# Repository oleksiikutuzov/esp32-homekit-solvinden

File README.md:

# esp32-homekit-led-strip
Native Apple HomeKit via an ESP32 for the IKEA SOLVINDEN lamp

Software is based on the [HomeSpan](https://github.com/HomeSpan/HomeSpan) library. Supports RGB or RGBW Neopixel LEDs.

_As usual, don't expect any warranties. I am just a hobbyist, not a professional. It works for me, but you take your own risk using it. I am not liable for any damage to your devices._

## Hardware

Custom PCB is designed for the project as well as a replacement base for the lamp. The base has holes for M3 threaded inserts.

From the original lamp, you only need the top part, which is good for diffusion. Be careful not to scratch it, as it sits pretty tight because the device is sealed.

## HomeKit functions

The device has two modes, which can be switched via the Eve app:
* Manual Control (manually set one single color)
* Rainbow (the device is changing colors)

*As they are custom characteristics, they are not visible in the Home app*

Characteristics values are saved to NVS, so they will be restored if the device loses power. 

## Software

Here you can see, which pins are used and pre-defined in the firmware:
```c++
 *                ESP-WROOM-32 Utilized pins
 *              ╔═════════════════════════════╗
 *              ║┌─┬─┐  ┌──┐  ┌─┐             ║
 *              ║│ | └──┘  └──┘ |             ║
 *              ║│ |            |             ║
 *              ╠═════════════════════════════╣
 *          +++ ║GND                       GND║ +++
 *          +++ ║3.3V                     IO23║ USED_FOR_NOTHING
 *              ║                         IO22║
 *              ║IO36                      IO1║ TX
 *              ║IO39                      IO3║ RX
 *              ║IO34                     IO21║
 *              ║IO35                         ║ NC
 *      RED_LED ║IO32                     IO19║
 *              ║IO33                     IO18║ 
 *              ║IO25                      IO5║
 *              ║IO26                     IO17║ NEOPIXEL
 *              ║IO27                     IO16║
 *              ║IO14                      IO4║
 *              ║IO12                      IO0║ +++, BUTTON
 *              ╚═════════════════════════════╝
```

The firmware can be built and flashed using the Arduino IDE.

For this, you will need to add ESP32 support to it.

Furthermore, you will also need to install the following libraries using the Library Manager:

* HomeSpan

And some libraries manually:

1. Go to this GitHub repo and download it as a ZIP - [ElegantOTA](https://github.com/ayushsharma82/ElegantOTA)
2. In Arduino IDE select "Sketch" -> "Include Library" and "Add .ZIP Library..." and select downloaded ZIP
3. Download and open this repository in Arduino IDE (or VSCode with Arduino extension)
4. Set the upload speed to 115200
5. Build, flash, and you're done

Instead of Arduino IDE OTA, the webserver update was implemented. You can flash binary at `http://[DEVICE IP]/update`.
There is a reboot link. Opening `http://[DEVICE IP]/reboot` will force the device to reboot. 

The device can also be controlled by the FLASH button on the board. More on [HomeSpan docs](https://github.com/HomeSpan/HomeSpan/blob/master/docs/UserGuide.md)

## Connect to HomeKit

1. Plug your LED Controller to power.
2. Press the FLASH button until the LED starts blinking rapidly and release it. Now it is in the configuration mode (More on [HomeSpan docs](https://github.com/HomeSpan/HomeSpan/blob/master/docs/UserGuide.md)). Press it two more times until the LED starts blinking 3 times in a row. This means mode 3 is chosen. Hold the button for 3-4 seconds once again and the WiFi AP will be started.
3. Go to WiFi settings on your iPhone/iPad and connect to the "HomeSpan-Setup" WiFi network.
4. You will choose your WiFi network and set the setup code for the accessory. 
5. Go to your Home app and select "Add Accessory"
6. Select "More Options" and you should see your LED Controller there.

## Todo

- [ ] Add physical button to control the device
- [ ] Add level shifter to the PCB for 5V on the data line for RGBW leds  

## References and sources

- @HomeSpan for ESP32 HomeKit firmware [GitHub link](https://github.com/HomeSpan/HomeSpan)

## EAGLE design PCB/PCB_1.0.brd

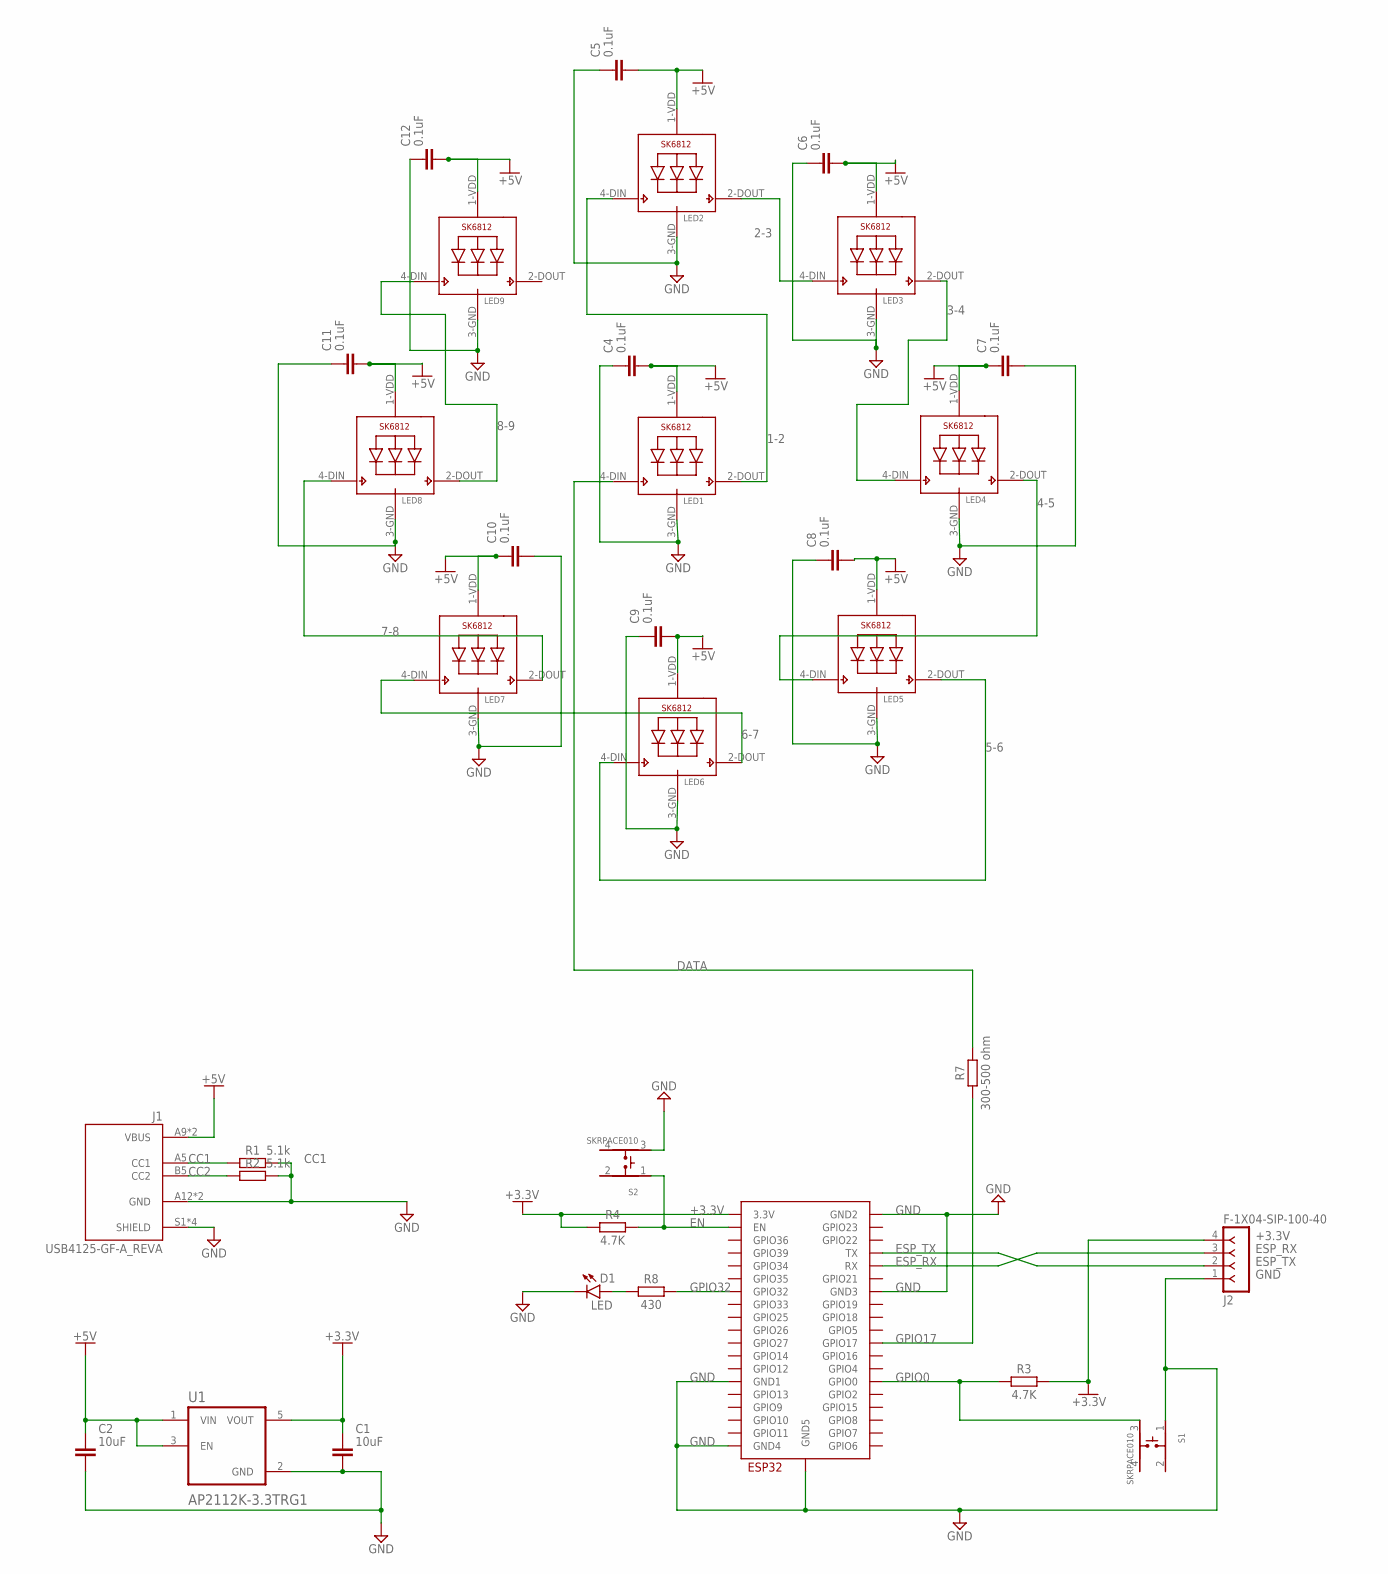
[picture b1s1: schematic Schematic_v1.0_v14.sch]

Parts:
C1, C2: 10uF; CAPC1608X85
C4, C5, C6, C7, C8, C9, C10, C11, C12: 0.1uF; CAPC1608X85
D1: LED; LEDC1608X80N_FLAT-R
J1: USB4125-GF-A_REVA; GCT_USB4125-GF-A_REVA
J2: F-1X04-SIP-100-40; SIP-100-04-40
LED1, LED2, LED3, LED4, LED5, LED6, LED7, LED8, LED9: SK6812_5050W; LED5050_W
R1, R2: 5.1k; RESC1608X60
R3, R4: 4.7K; RESC1608X60
R7: 300-500 ohm; RESC1608X60
R8: 430; RESC1608X60
S1, S2: SKRPACE010; SW_SKRPACE010
U1: AP2112K-3.3TRG1; SOT95P285X140-5N
U2: ESP32-WROOM

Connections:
1-2: LED1.2-DOUT (DO), LED2.4-DIN (DI)
2-3: LED2.2-DOUT (DO), LED3.4-DIN (DI)
3-4: LED3.2-DOUT (DO), LED4.4-DIN (DI)
4-5: LED4.2-DOUT (DO), LED5.4-DIN (DI)
5-6: LED5.2-DOUT (DO), LED6.4-DIN (DI)
6-7: LED6.2-DOUT (DO), LED7.4-DIN (DI)
7-8: LED7.2-DOUT (DO), LED8.4-DIN (DI)
8-9: LED8.2-DOUT (DO), LED9.4-DIN (DI)
+3.3V: C1.1, J2.4, R3.2, R4.1, U1.5 (VOUT), U2.3V3 (3.3V)
+5V: C2.1, C4.2, C5.2, C6.2, C7.1, C8.2, C9.2, C10.1, C11.2, C12.2, J1.A9 (VBUS), J1.B9 (VBUS), LED1.1-VDD (VDD), LED2.1-VDD (VDD), LED3.1-VDD (VDD), LED4.1-VDD (VDD), LED5.1-VDD (VDD), LED6.1-VDD (VDD), LED7.1-VDD (VDD), LED8.1-VDD (VDD), LED9.1-VDD (VDD), U1.1 (VIN), U1.3 (EN)
CC1: J1.A5 (CC1), R1.1
CC2: J1.B5 (CC2), R2.1
DATA: LED1.4-DIN (DI), R7.2
EN: R4.2, S2.1, U2.EN
ESP_RX: J2.3, U2.RX
ESP_TX: J2.2, U2.TX
GND: C1.2, C2.2, C4.1, C5.1, C6.1, C7.2, C8.1, C9.1, C10.2, C11.1, C12.1, D1.C, J1.A12 (GND), J1.B12 (GND), J1.S1 (SHIELD), J1.S2 (SHIELD), J1.S3 (SHIELD), J1.S4 (SHIELD), J2.1, LED1.3-GND (GND), LED2.3-GND (GND), LED3.3-GND (GND), LED4.3-GND (GND), LED5.3-GND (GND), LED6.3-GND (GND), LED7.3-GND (GND), LED8.3-GND (GND), LED9.3-GND (GND), R1.2, R2.2, S1.1, S2.3, U1.2 (GND), U2.GND1, U2.GND2, U2.GND3, U2.GND4, U2.GND5
GPIO0: R3.1, S1.3, U2.IO0 (GPIO0)
GPIO17: R7.1, U2.IO17 (GPIO17)
GPIO32: R8.2, U2.IO32 (GPIO32)
LED: D1.A, R8.1

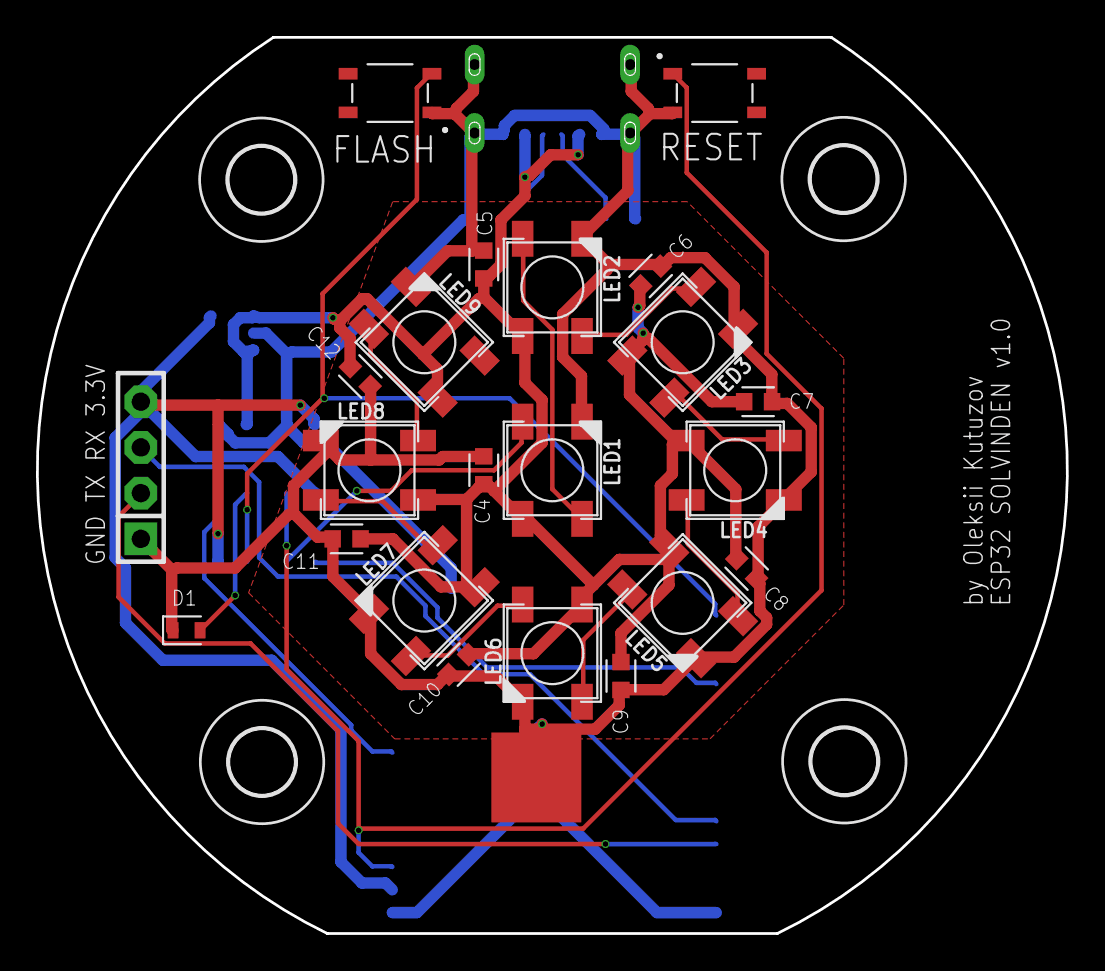
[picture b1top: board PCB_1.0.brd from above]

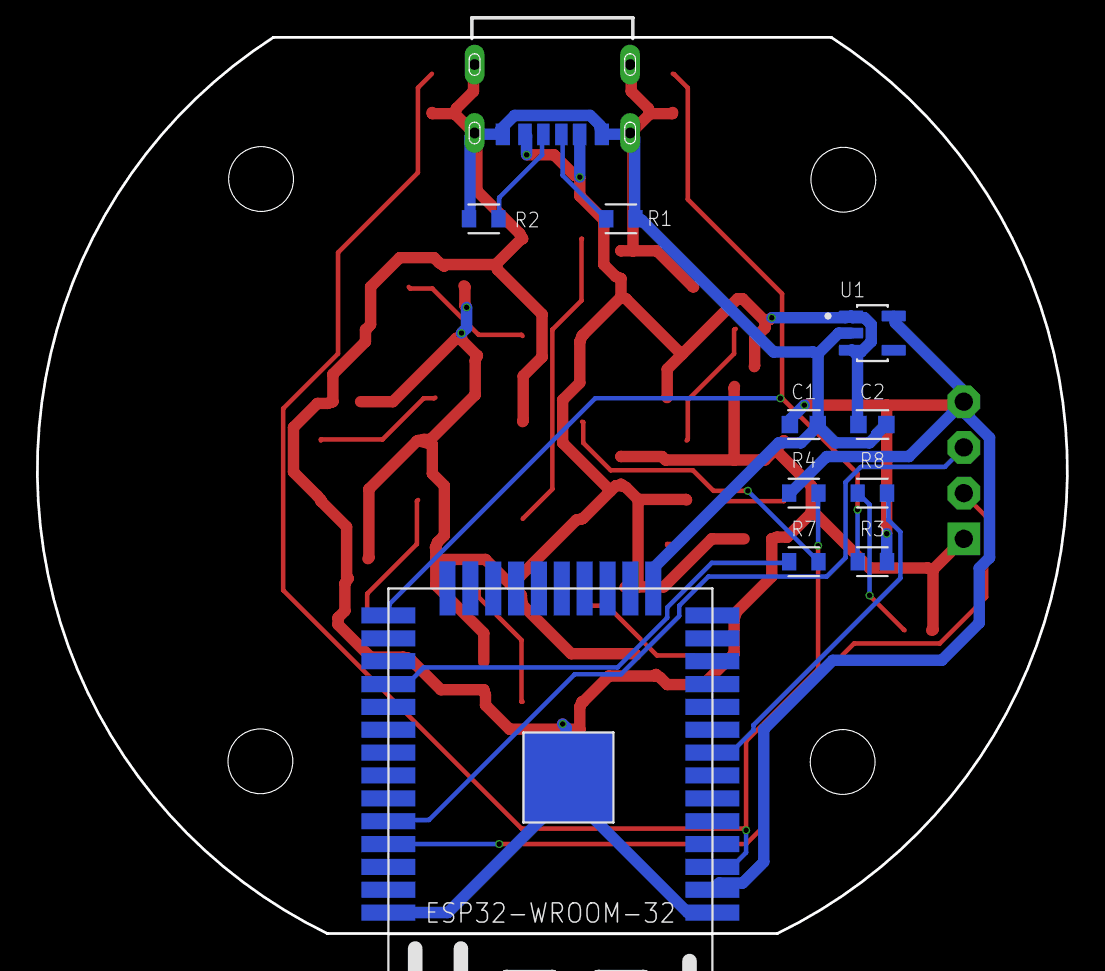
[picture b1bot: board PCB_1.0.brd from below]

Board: 2 copper layers, 57.2 x 49.8 mm, 37 parts (11 on the bottom side), 21 nets.

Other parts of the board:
H3, H5, H7, H9: MOUNT-HOLE3.6; 3,6

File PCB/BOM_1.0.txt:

Part Value             Device                   Package               Description                                                                  AVAILABILITY CATEGORY  
C1   10uF              C_CHIP-0603(1608-METRIC) CAPC1608X85           Capacitor - Generic                                                                       Capacitor 
C2   10uF              C_CHIP-0603(1608-METRIC) CAPC1608X85           Capacitor - Generic                                                                       Capacitor 
C4   0.1uF             C_CHIP-0603(1608-METRIC) CAPC1608X85           Capacitor - Generic                                                                       Capacitor 
C5   0.1uF             C_CHIP-0603(1608-METRIC) CAPC1608X85           Capacitor - Generic                                                                       Capacitor 
C6   0.1uF             C_CHIP-0603(1608-METRIC) CAPC1608X85           Capacitor - Generic                                                                       Capacitor 
C7   0.1uF             C_CHIP-0603(1608-METRIC) CAPC1608X85           Capacitor - Generic                                                                       Capacitor 
C8   0.1uF             C_CHIP-0603(1608-METRIC) CAPC1608X85           Capacitor - Generic                                                                       Capacitor 
C9   0.1uF             C_CHIP-0603(1608-METRIC) CAPC1608X85           Capacitor - Generic                                                                       Capacitor 
C10  0.1uF             C_CHIP-0603(1608-METRIC) CAPC1608X85           Capacitor - Generic                                                                       Capacitor 
C11  0.1uF             C_CHIP-0603(1608-METRIC) CAPC1608X85           Capacitor - Generic                                                                       Capacitor 
C12  0.1uF             C_CHIP-0603(1608-METRIC) CAPC1608X85           Capacitor - Generic                                                                       Capacitor 
D1   LED               CHIP-FLAT-R_0603-0.80MM  LEDC1608X80N_FLAT-R                                                                                             LED       
J1   USB4125-GF-A_REVA USB4125-GF-A_REVA        GCT_USB4125-GF-A_REVA USB 2.0 Type C Receptacle, Horizontal, SMT, For Power charging  Check prices Warning                
J2   F-1X04-SIP-100-40 F-1X04-SIP-100-40        SIP-100-04-40         FEMALE HEADER                                                                                       
LED1                   SK6812_5050W             LED5050_W                                                                                                                  
LED2                   SK6812_5050W             LED5050_W                                                                                                                  
LED3                   SK6812_5050W             LED5050_W                                                                                                                  
LED4                   SK6812_5050W             LED5050_W                                                                                                                  
LED5                   SK6812_5050W             LED5050_W                                                                                                                  
LED6                   SK6812_5050W             LED5050_W                                                                                                                  
LED7                   SK6812_5050W             LED5050_W                                                                                                                  
LED8                   SK6812_5050W             LED5050_W                                                                                                                  
LED9                   SK6812_5050W             LED5050_W                                                                                                                 
R1   5.1k              R_CHIP-0603(1608-METRIC) RESC1608X60           Resistor Fixed - Generic                                                                  Resistor  
R2   5.1k              R_CHIP-0603(1608-METRIC) RESC1608X60           Resistor Fixed - Generic                                                                  Resistor  
R3   4.7K              R_CHIP-0603(1608-METRIC) RESC1608X60           Resistor Fixed - Generic                                                                  Resistor  
R4   4.7K              R_CHIP-0603(1608-METRIC) RESC1608X60           Resistor Fixed - Generic                                                                  Resistor  
R7   300-500 ohm       R_CHIP-0603(1608-METRIC) RESC1608X60           Resistor Fixed - Generic                                                                  Resistor  
R8   430               R_CHIP-0603(1608-METRIC) RESC1608X60           Resistor Fixed - Generic                                                                  Resistor  
S1   SKRPACE010        SKRPACE010               SW_SKRPACE010         Switch Tactile N.O. SPST Button J-Bend 0.05A 16VDC 2.55N SMD Automotive T/R                         
S2   SKRPACE010        SKRPACE010               SW_SKRPACE010         Switch Tactile N.O. SPST Button J-Bend 0.05A 16VDC 2.55N SMD Automotive T/R                         
U1   AP2112K-3.3TRG1   AP2112K-3.3TRG1          SOT95P285X140-5N      AP2112 Series 0.6 A 3.3 V Fixed Output SMT LDO Linear Regulator - SOT23-5                           
U2   ESP32-WROOM       ESP32-WROOM              ESP32-WROOM

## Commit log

2022-05-30 Add build task
2022-05-30 Add .gitignore and .clang-format
2022-05-30 Add settings files
2022-05-30 Add sketch from led_strip project
2022-05-30 Add README
2022-05-30 Add Base 3D model
2022-05-30 Add more hardware files
2022-05-30 Update vscode settings
2022-05-30 Remove unneeded code
2022-07-08 Add RGBW strip support, remove third effect, misc
2022-07-08 Serial number field shows mac address of ESP32
2022-07-08 Update vscode config
2022-07-08 Update hardware files names
2022-08-09 Switch from ESPAsyncWebServer to WebServer
2022-08-09 Add server handle to loop
2022-08-09 Update settings
2022-09-03 Add OTA capability
2022-09-03 Quick fix
2022-09-03 Quick fix binary
2022-09-03 Different builds for RGB and RGBW
2022-09-03 Test update
2022-09-03 Fix update URLs, minor adjustments
2022-09-03 Update version
2022-09-03 Increase update check interval to 1 hour
2022-09-04 Switch to PlatformIO
2022-09-04 Switch to PlatformIO build
2022-09-04 temp
2022-09-04 move main.cpp
2022-09-04 Included fixed for PlatformIO HomeSpan library
2022-09-04 Remove library
2022-09-04 Add Homespan as a submodule
2022-09-05 Remove submodule
2022-09-05 Update platformio config
2022-09-05 Update PlatformIO config (#19)
    * Remove submodule
    * Update platformio config
    * Update build.yml
2022-10-07 Update config
2022-10-08 Initial changes to enable white light w/ long dim
2022-11-14 Remove include

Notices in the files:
parts and their libraries:
con-headers-jp: Copyright (C) 2008, Bob Starr
